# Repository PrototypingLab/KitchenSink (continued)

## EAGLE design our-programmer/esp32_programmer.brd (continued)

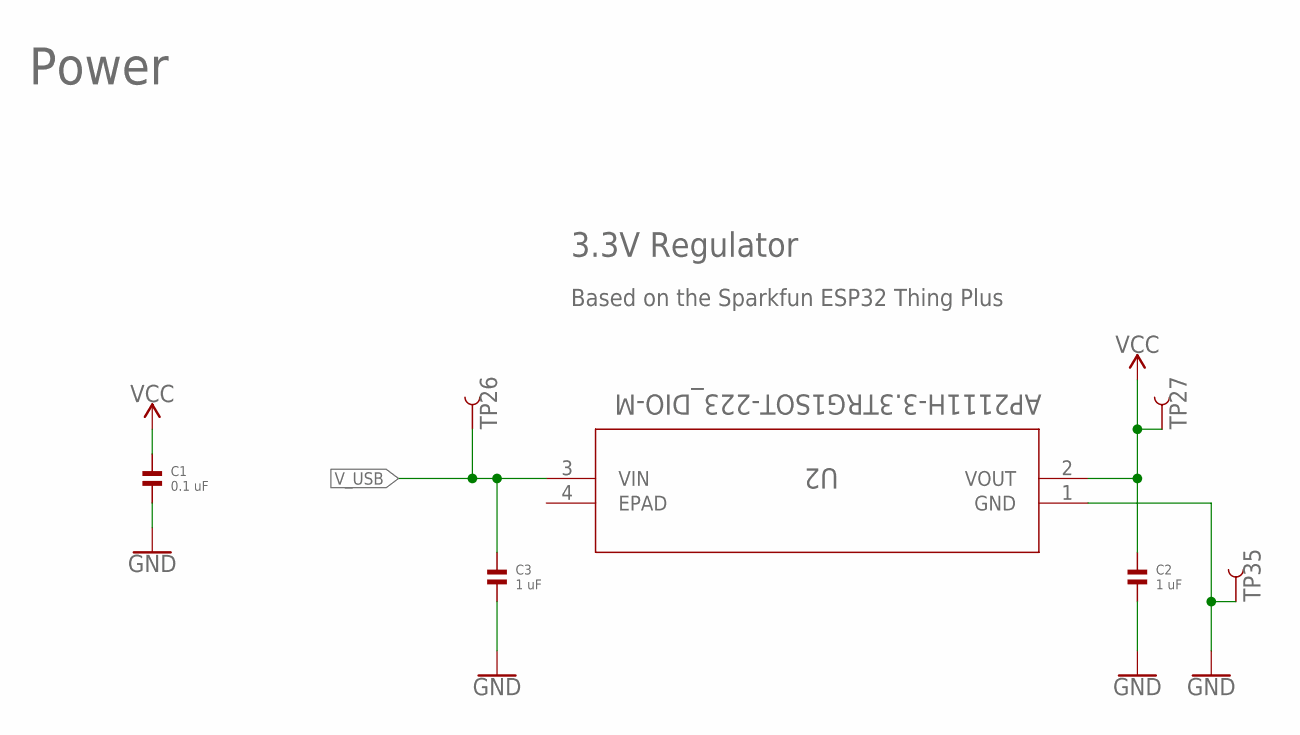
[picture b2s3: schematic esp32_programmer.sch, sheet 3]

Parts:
C1: 0.1 uF; 1206
C2, C3: 1 uF; 1206
TP26, TP27, TP35: TEST-POINT3X5; PAD.03X.05
U2: AP2111H-3.3TRG1SOT-223_DIO-M; SOT-223_DIO-M

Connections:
GND: C1.2, C2.2, C3.2, TP35.P$1, U2.1 (GND); also elsewhere on the board
VCC: C1.1, C2.1, TP27.P$1, U2.2 (VOUT); also elsewhere on the board
V_USB: C3.1, TP26.P$1, U2.3 (VIN); also elsewhere on the board

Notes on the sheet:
Power
3.3V Regulator
Based on the Sparkfun ESP32 Thing Plus

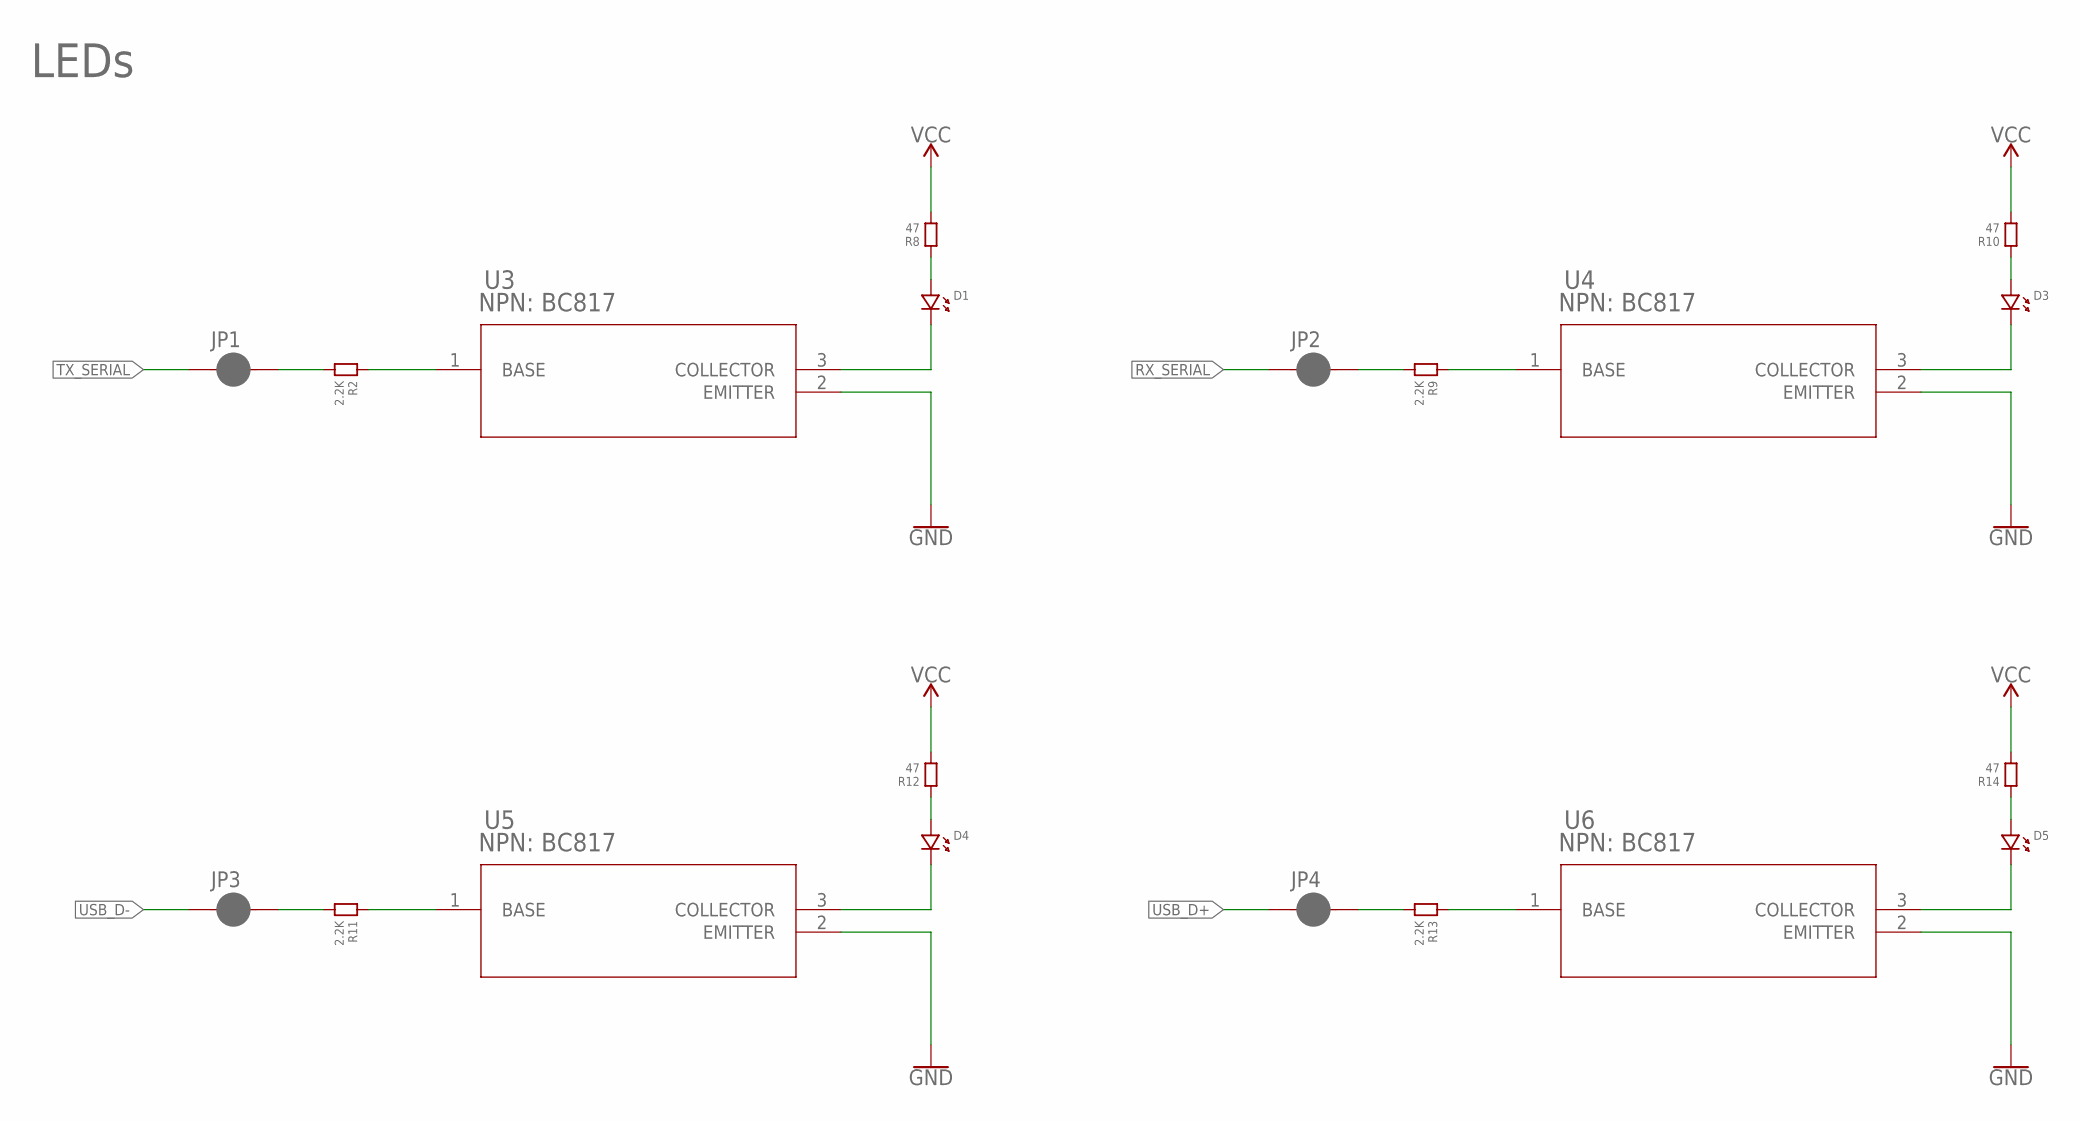
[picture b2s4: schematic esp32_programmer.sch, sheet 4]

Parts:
D1, D3, D4, D5: LED.1206; 1206.LED
JP1, JP2, JP3, JP4: JUMPER-SMT_2_NC_PASTE_SILK; SMT-JUMPER_2_NC_PASTE_SILK
R2, R9, R11, R13: 2.2K; 1206
R8, R10, R12, R14: 47; 1206
U3, U4, U5, U6: NPN: BC817; SOT-23-3_1P4X3P040_ONS-M

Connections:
BLEP1: D4.P$2 (2), U5.3 (COLLECTOR)
BLEP2: D5.P$2 (2), U6.3 (COLLECTOR)
BLEP3: D1.P$2 (2), U3.3 (COLLECTOR)
BLEP4: D3.P$2 (2), U4.3 (COLLECTOR)
GND: U3.2 (EMITTER), U4.2 (EMITTER), U5.2 (EMITTER), U6.2 (EMITTER); also elsewhere on the board
unnamed: JP1.2, R2.2
unnamed: JP2.2, R9.2
unnamed: R2.1, U3.1 (BASE)
unnamed: D1.P$1 (1), R8.1
unnamed: R9.1, U4.1 (BASE)
unnamed: D3.P$1 (1), R10.1
unnamed: JP3.2, R11.2
unnamed: R11.1, U5.1 (BASE)
unnamed: D4.P$1 (1), R12.1
unnamed: JP4.2, R13.2
unnamed: R13.1, U6.1 (BASE)
unnamed: D5.P$1 (1), R14.1
RX_SERIAL: JP2.1; also elsewhere on the board
TX_SERIAL: JP1.1; also elsewhere on the board
USB_D+: JP4.1; also elsewhere on the board
USB_D-: JP3.1; also elsewhere on the board
VCC: R8.2, R10.2, R12.2, R14.2; also elsewhere on the board

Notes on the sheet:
LEDs

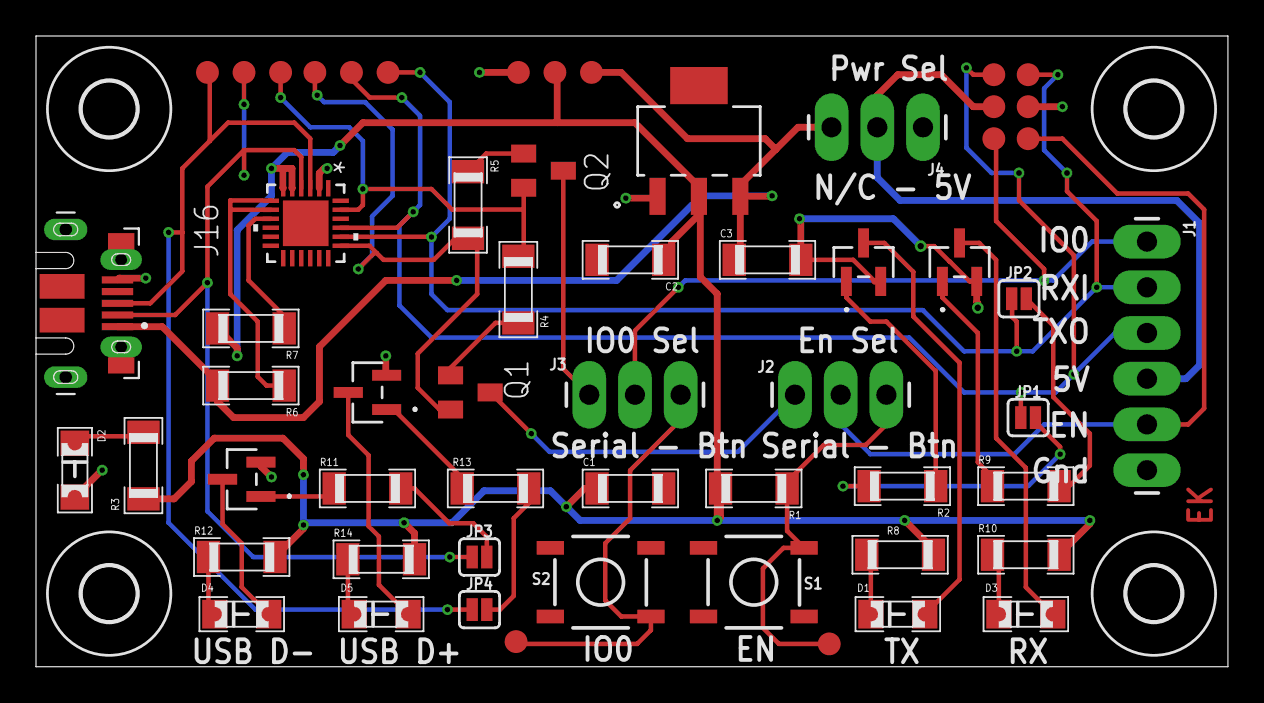
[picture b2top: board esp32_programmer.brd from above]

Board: 2 copper layers, 66.2 x 35.0 mm, 62 parts (0 on the bottom side), 38 nets.

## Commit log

2022-12-12 Schematic complete for ESP32-Wroom board
2022-12-20 Added DC in and 5V regulator, Started initial pcb layout and routing
2022-12-23 Circuit layout complete for mini version
2022-12-23 Schematic and start of circuit board layout for programmer board
2022-12-24 Programmer board complete
2022-12-28 Archiving previous revisions of board
2022-12-28 Updates to larger kitchen sink files
2022-12-28 Kitchen Sink Mini v1.2 board complete
2022-12-28 Changelog documentation
2022-12-29 Moving previous version to archive
2022-12-29 Programmer v1.1 added
2022-12-29 Update changelog for Our Programmer board
2023-01-07 Latest revision of kitchen sink mini v1.2
2023-01-07 Moving previous revision to archive
2023-01-07 Removing old gerber
2023-01-07 Moving v1.2 to archive
2023-01-07 Added v1.3
2023-01-07 Documenting v1.3
2023-01-07 Cleaning
